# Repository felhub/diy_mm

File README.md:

# diy_mm

Low cost (less than 10€) measurement microphone powered by +48V phantom power using a cheap electret capsule.
### Technical Data

| spec                  | value                 | unit          | measured  |
|:---------------------:|:---------------------:|:-------------:|:---------:|
| Frequency Response    | 20 to 20000 &pm; 3dB  | Hz            | n         |
| Polar Pattern         | Omnidirectional       | -             | n         |
| Sensititvity          | 0.013                 | V/Pa @ 1kHz   | y         |
| Power requirements    | +12 to +48            | V             | y         |
| Max acoustic input    | 140dB                 | SPL           | y         |
| Output                | XLR-3 (balanced)      | -             | -         |
| Output Impedance      | 100                   | Ohm           | y         |
| Signal to Noise       | 60dBA                 | SPL           | n         |
| Temp Operating Range  | -20 to 70             | °C            | n         |
| Dimensions L x D      | 107.2 x 12            | mm            | y         |
| Weight                | 16 (120 with 3m cable)| g             | y         |

### Measured Frequency Response

## Impedance Converter and capsule adapter (kicad)

The impedance converter is based on an electret mic preamp from [Rod Elliot](https://sound-au.com), big thanks to the work he does on his site. He also has a store, where you can buy his original PCB for this amp, and many others. You can also donate there.  

Some changes were made to fit the converter to the capsule and to use smaller capacitors to fit it into the housing. Unfortunately these changes also effect the performance slightly.

In order to connect the PCB to the capsule and also to fix the capsule in place a small adapter PCB is used. This PCB is clamped in the 3d printed housing an soldered onto the converters PCB.

| main_board | capsule_adapter |
|:-----------------------------:|:----------------------------------:|
|  |  |

## LTSpice Simulation (simulation)

Alongside the changes of the converter design a LTSpice simulation was conducted. The obtained result is very good, showing linearity of &pm;0.1dB and a very true phase slowly rising below 100Hz to reach \~13&deg; at 20Hz. The impedance converter also features a signal amplification of \~3dB.

## 3D printed parts (3dfiles)

The fixture for capsule, impedance converter and strain relief if the cable are accomplished by three 3d printed parts. Using a 0.25mm nozzle the parts can be printed very accurately to perfectly fit the shielding aluminium tube using three o-rings.

Through a hole in the chassis at the strain relief side, the shielding can be fed through in order to touch the aluminium tube. The hole assembly slides tightly inside and is just hold by friction. To get it back out one has to firstly pull on the cable slightly, after the first o-ring is out one should pull on the plastic to fully slide out the main assembly.

## Array configuration

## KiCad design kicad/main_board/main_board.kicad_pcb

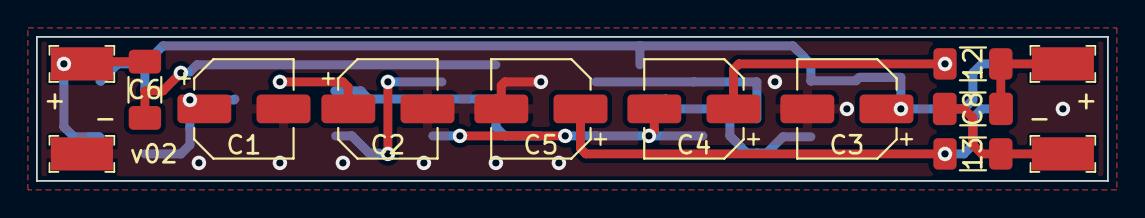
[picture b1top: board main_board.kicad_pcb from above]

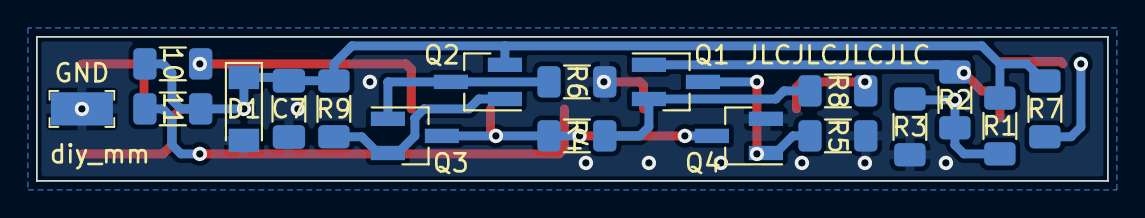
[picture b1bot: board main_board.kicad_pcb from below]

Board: 2 copper layers, 59.5 x 8.0 mm, 31 parts (18 on the bottom side), 15 nets.

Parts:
C1, C2, C3, C4, C5: 33u; CP_Elec_5x5.4
C6: 1u; C_1206_3216Metric_Pad1.33x1.80mm_HandSolder
C7: 100n; C_1206_3216Metric_Pad1.33x1.80mm_HandSolder
C8: 1n; C_1206_3216Metric_Pad1.33x1.80mm_HandSolder
D1: 9.1V; D_MiniMELF
J1: mic+; PC_TEST_POINT_SMD
J2: mic-; PC_TEST_POINT_SMD
J3: XLR2; PC_TEST_POINT_SMD
J4: XLR1; PC_TEST_POINT_SMD
J5: XLR3; PC_TEST_POINT_SMD
Q1, Q2, Q3: BC859C; SOT-23_Handsoldering
Q4: BC849C; SOT-23_Handsoldering
R1, R2: 100k; R_1206_3216Metric_Pad1.30x1.75mm_HandSolder
R3, R5, R6: 33k; R_1206_3216Metric_Pad1.30x1.75mm_HandSolder
R4, R8: 10k; R_1206_3216Metric_Pad1.30x1.75mm_HandSolder
R7, R10, R11: 2.2k; R_1206_3216Metric_Pad1.30x1.75mm_HandSolder
R9: 220; R_1206_3216Metric_Pad1.30x1.75mm_HandSolder
R12, R13: 100; R_1206_3216Metric_Pad1.30x1.75mm_HandSolder

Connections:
+10V: C3.1, C7.1, D1.1 (K), Q2.2 (E), R1.1, R7.1, R9.2, R10.2, R11.2
GND: C1.2, C2.2, C3.2, C5.2, C7.2, D1.2 (A), J2.1, J4.1, Q4.2 (E), R3.2, R5.2, R6.2
unnamed: C1.1, R1.2, R2.2, R3.1
unnamed: C2.1, R8.2
unnamed: C4.1, R10.1, R12.2
unnamed: C4.2, Q3.3 (C), Q4.3 (C), R4.2
unnamed: C5.1, R11.1, R13.2
unnamed: C6.1, J1.1, R7.2
unnamed: C6.2, Q1.1 (B), R2.1
unnamed: C8.1, J3.1, R12.1
unnamed: C8.2, J5.1, R13.1
unnamed: Q1.2 (E), R4.1, R8.1
unnamed: Q1.3 (C), Q4.1 (B), R5.1
unnamed: Q2.1 (B), Q3.2 (E), R9.1
unnamed: Q2.3 (C), Q3.1 (B), R6.1

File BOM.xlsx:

diy_mm
Bill of Materials
 |  |  |  |  |  |  |  |  | #NAME?
Reference | Value | Footprint | Name | Comment | Supplier | Art. Nr. | Price/Pcs | Pcs | Total | Status
electric components
MK |  |  | CMA-4544PF-W | capsule | mouser.at | 490-CMA-4544PF-W | 0.62 | 1 | 0.62
Q1-Q3 |  | SOT-23-3 BEC | BC859C | pnp | conrad.at | 153145 | 0.08 | 3 | 0.24
Q4 |  | SOT-23-3 BEC | BC849C | npn | conrad.at | 152907 | 0.09 | 1 | 0.09
C1-C5 | 33u | 5x5.5 | WCAP-ASLI 865080442006 | 25v | mouser.at | 710-865080442006 | 0.16400000000000001 | 5 | 0.82000000000000006
C6 | 1u | 1206 | MLCC 885012208093 | ceramic | mouser.at | 710-885012208093 | 0.16200000000000001 | 1 | 0.16200000000000001
C7 | 100n | 1206 | MLCC 885012208087 | ceramic | mouser.at | 710-885012208087 | 0.09 | 1 | 0.09
C8 | 1n | 1206 | MLCC 885012208075 | ceramic | mouser.at | 710-885012208075 | 7.4999999999999997E-2 | 1 | 7.4999999999999997E-2
D1 | 10V | SOD-80C | Vishay 78-BZT55C9V1 | zener | mouser.at | 78-BZT55C9V1 | 0.08 | 1 | 0.08
R1-R2 | 100k | 1206 |  | 1% 0.25W | mouser.at | 652-CR1206FX-1003ELF | 1.2999999999999999E-2 | 2 | 2.5999999999999999E-2
R3-R6 | 33k | 1206 |  | 1% 0.25W | mouser.at | 652-CR1206FX-3302ELF | 2.5999999999999999E-2 | 4 | 0.104
R8 | 10k | 1206 |  | 1% 0.25W | mouser.at | 652-CR1206FX-1002ELF | 1.2999999999999999E-2 | 1 | 1.2999999999999999E-2
R9 | 220 | 1206 |  | 1% 0.25W | mouser.at | 652-CR1206FX-2200ELF | 3.2000000000000001E-2 | 1 | 3.2000000000000001E-2
R7, R10-R11 | 2.2k | 1206 |  | 1% 0.25W | mouser.at | 652-CR1206FX-2201ELF | 1.7999999999999999E-2 | 3 | 5.3999999999999992E-2
R12-R13 | 100 | 1206 |  | 1% 0.25W | mouser.at | 652-CR1206FX-1000ELF | 1.4999999999999999E-2 | 2 | 0.03
 |  |  | Sommer Cable The Goblin BK | per meter | thomann.de | 160823 | 1.0900000000000001 | 3 | 3.2700000000000005
 |  |  | Neutrik NC3 MXX | male XLR | thomann.de | 182696 | 2.88 | 1 | 2.88
mechanical components
 |  |  | Rundrohr Alu silber eloxiert 12x1 | per meter | hornbach.at | 6449190 | 3.04 | 0.104 | 0.31616
 |  |  |  | incl. Shipping | jlcpcb.com |  | 0.17399999999999999 | 1 | 0.17399999999999999
 |  |  | NBR-70 O-Ring 6.00x1.50Ø | 3x | persicaner.at | 1571483 | 2.9300000000000003E-2 | 3 | 8.7900000000000006E-2
 |  |  | cable_clamp | 3d print |  |  | 0.03 | 1 | 0.03
 |  |  | capsule_clamp | 3d print |  |  | 0.02 | 1 | 0.02
 |  |  | chassis_oring | 3d print |  |  | 7.0000000000000007E-2 | 1 | 7.0000000000000007E-2

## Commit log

2022-01-31 New try with readme file
2022-02-01 first full kicad push
2022-02-03 redesign for KiCad 6.0.1
2022-02-04 capsule adapter added
2022-02-04 remove test
2022-02-04 fix wrong push with all files
2022-02-04 fixed silk at mounting holes
2022-02-04 kicad headers updated, small simulation updates
2022-02-05 new R labeling, capsule pwr 2.2k
2022-02-05 small updates and new readme
2022-02-05 new BOM design
2022-02-05 readme updates
2022-02-05 pcb images view correction
2022-02-05 .JPG -> .jpg
2022-02-06 BOM updates
2022-02-07 references in readme
2022-02-07 new readme
2022-02-13 new LTSpice graphics
2022-02-13 new names and solder jig
2022-02-16 change print layout
2022-02-18 make electronics fully removeable
2022-02-19 minor model tweaks
2022-02-22 gain resistor R8 to 10k
2022-02-28 updated images
2022-03-06 new technical data
2022-03-06 hardware update
2022-03-06 added weight
2022-03-07 fixed naming C5->C2
2022-03-10 ignore
2022-03-10 freq tolerance
2022-03-11 measured sensitivity
2022-03-14 array added
2022-03-24 rotatet array img
